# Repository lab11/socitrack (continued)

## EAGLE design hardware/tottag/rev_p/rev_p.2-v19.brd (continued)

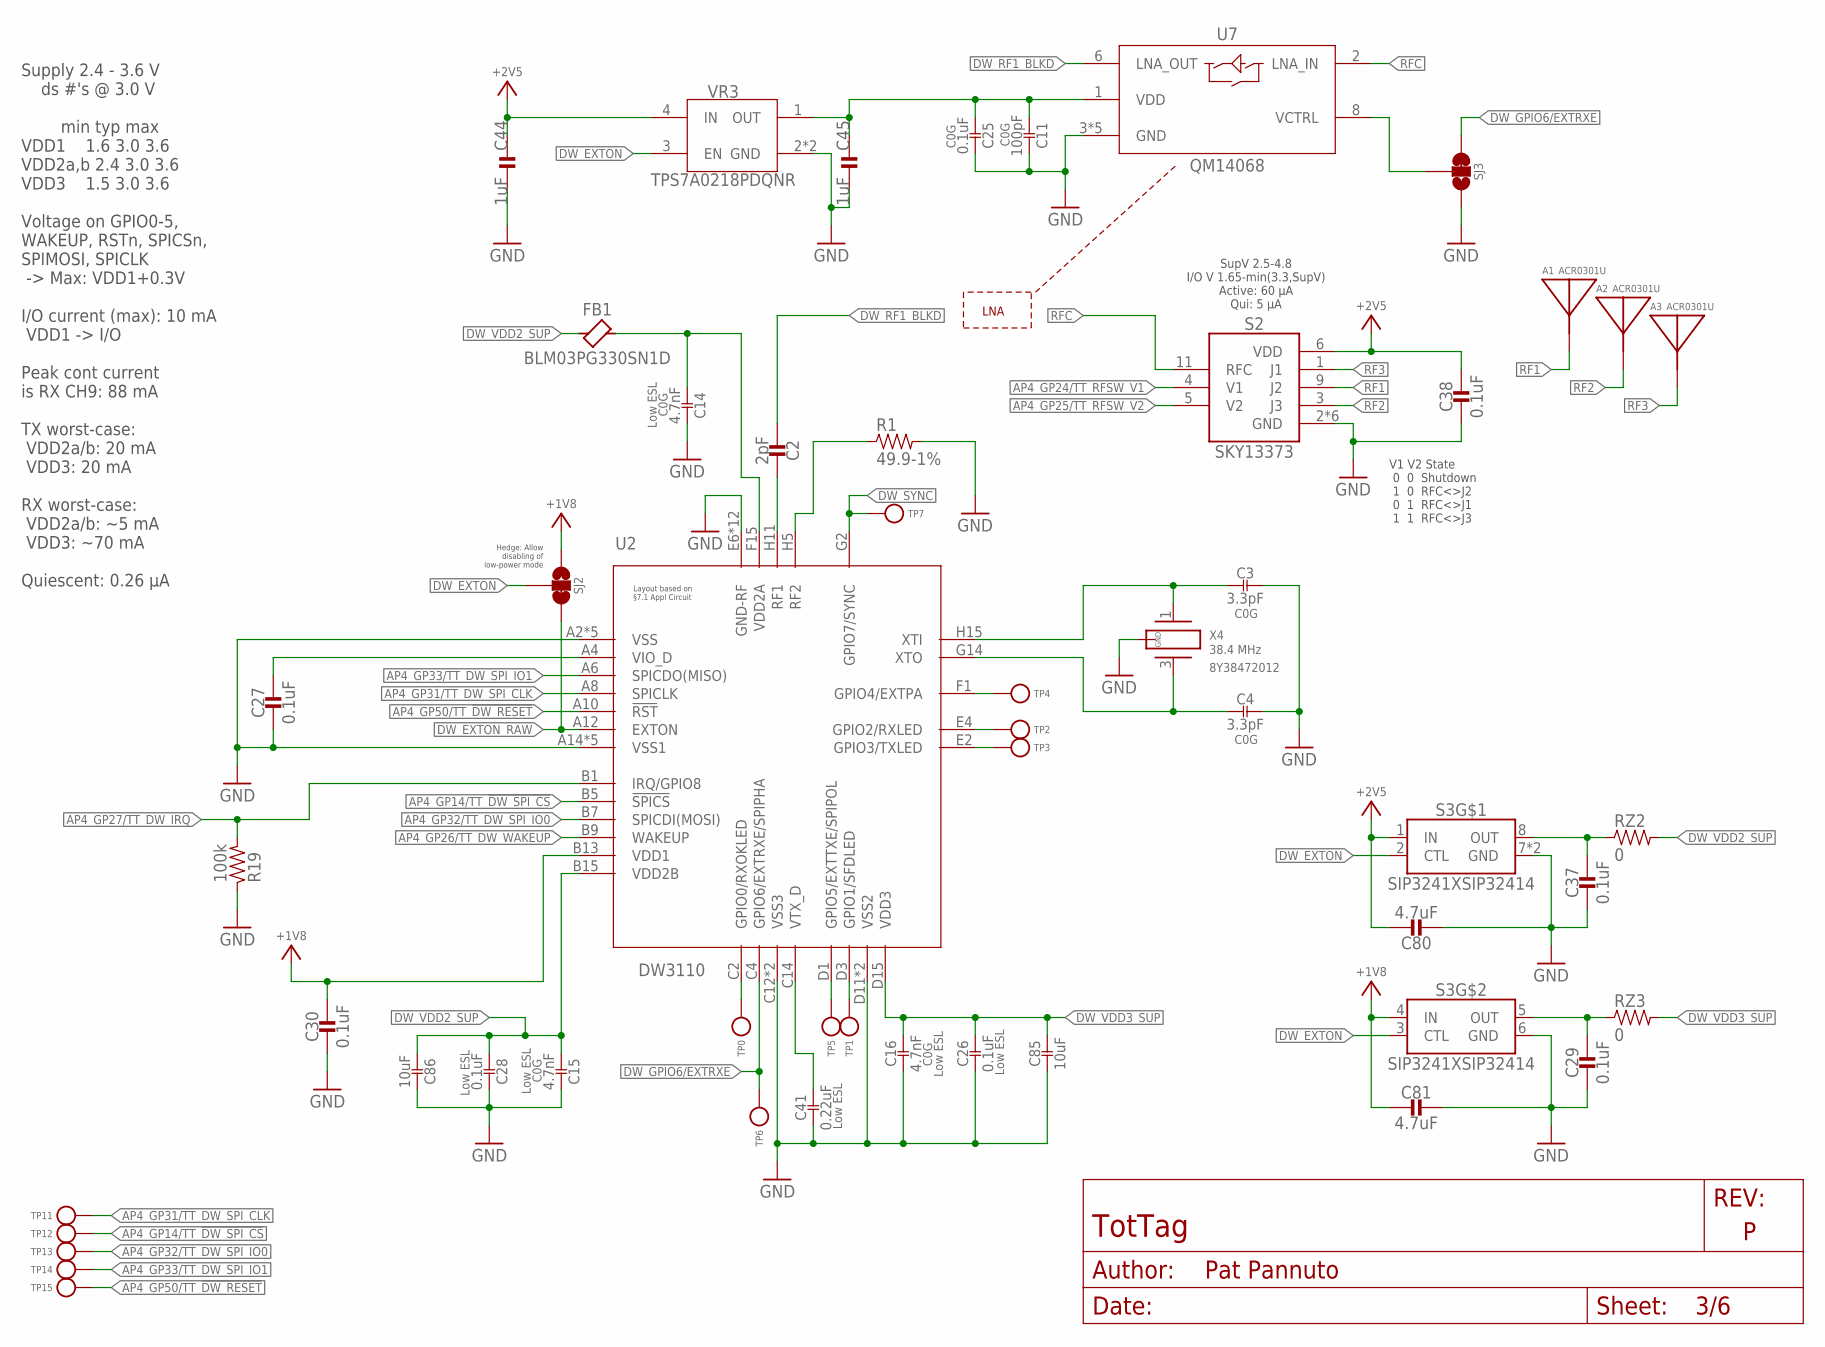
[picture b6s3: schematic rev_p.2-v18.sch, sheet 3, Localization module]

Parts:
A1, A2, A3: ACR0301U
C2: 2pF; 0201_CAP; MPN CBR02C209A5GAC
C3, C4: 3.3pF; SMD_2012M-0805US-C; MPN 600F3R3BT250XT
C11: 100pF; SMD_1005M-0402US-C; MPN C0402C101J3GACTU
C14, C15, C16: 4.7nF; SMD_1608M-0603US-C; MPN C0603C472J5GACTU
C25: 0.1uF; SMD_3216M-1206US-C; MPN GRM31C5C1H104JA01L
C26, C28: 0.1uF; SMD_1608M-0603US-C; MPN C1608X7R1H104K080AA
C27, C29, C30, C37, C38: 0.1uF; 0402_CAP; MPN CL05A104KP5NNNC
C41: 0.22uF; SMD_1608M-0603US-C; MPN C1608X7R1H224K080AB
C44, C45: 1uF; 0201_CAP; MPN GRM033R61A105ME44D
C80, C81: 4.7uF; 0603_CAP; MPN C1608X7S1A475K080AC
C85, C86: 10uF; SMD_1608M-0603US-C; MPN CM105X5R106M25AT
FB1: BLM03PG330SN1D; 0201_FB; MPN BLM03PG330SN1D
R1: 49.9-1%; 0201_RES; MPN ERJ-1GNF49R9C
R19: 100k; 0402_RES; MPN RT0402BRE07100KL
RZ2, RZ3: 0; 0603-RES; MPN RMCF0603ZT0R00
S2: SKY13373
S3: SIP3241XSIP32414; TDFN2X2X0P6-8
SJ2, SJ3: JUMPER-SMT_3_1-NC_TRACE_SILK; SMT-JUMPER_3_1-NC_TRACE_SILK
TP0, TP1, TP2, TP3, TP4, TP5, TP6, TP7, TP11, TP12, TP13, TP14, TP15: TEST-POINT; PAD.03X.03
U2: DW3110; WLCSP52
U7: QM14068
VR3: TPS7A0218PDQNR; 4-XDFN-EP
X4: TXC-8Y; MPN 8Y38472012

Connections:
+1V8: C30.1, C81.2, S3.4 (IN), SJ2.1, U2.B13 (VDD1); also elsewhere on the board
+2V5: C38.1, C44.P$1 (1), C80.1, S2.6 (VDD), S3.1 (IN), VR3.4 (IN); also elsewhere on the board
AP4_GP14/TT_!DW_SPI_CS: TP12.P$1, U2.B5 (!SPICS); also elsewhere on the board
AP4_GP24/TT_RFSW_V1: S2.4 (V1); also elsewhere on the board
AP4_GP25/TT_RFSW_V2: S2.5 (V2); also elsewhere on the board
AP4_GP26/TT_DW_WAKEUP: U2.B9 (WAKEUP); also elsewhere on the board
AP4_GP27/TT_DW_IRQ: R19.2, U2.B1 (IRQ/GPIO8); also elsewhere on the board
AP4_GP31/TT_DW_SPI_CLK: TP11.P$1, U2.A8 (SPICLK); also elsewhere on the board
AP4_GP32/TT_DW_SPI_IO0: TP13.P$1, U2.B7 (SPICDI(MOSI)); also elsewhere on the board
AP4_GP33/TT_DW_SPI_IO1: TP14.P$1, U2.A6 (SPICDO(MISO)); also elsewhere on the board
AP4_GP50/TT_!DW_RESET: TP15.P$1, U2.A10 (!RST); also elsewhere on the board
DW_EXTON: S3.2 (CTL), S3.3 (CTL), SJ2.2, VR3.3 (EN)
DW_EXTON_RAW: SJ2.3, U2.A12 (EXTON)
DW_GPIO4: TP4.P$1, U2.F1 (GPIO4/EXTPA)
DW_GPIO5: TP5.P$1, U2.D1 (GPIO5/EXTTXE/SPIPOL)
DW_GPIO6/EXTRXE: SJ3.3, TP6.P$1, U2.C4 (GPIO6/EXTRXE/SPIPHA)
DW_RF1: C2.P$1 (1), U2.H11 (RF1)
DW_RF1_BLKD: C2.P$2 (2), U7.6 (LNA_OUT)
DW_RF2: R1.1, U2.H5 (RF2)
DW_RXLED: TP2.P$1, U2.E4 (GPIO2/RXLED)
DW_RXOKLED: TP0.P$1, U2.C2 (GPIO0/RXOKLED)
DW_SFDLED: TP1.P$1, U2.D3 (GPIO1/SFDLED)
DW_SYNC: TP7.P$1, U2.G2 (GPIO7/SYNC)
DW_TXLED: TP3.P$1, U2.E2 (GPIO3/TXLED)
DW_VDD2A: C14.P$1, FB1.P$2, U2.F15 (VDD2A)
DW_VDD2_PWROUT: C37.1, RZ2.1, S3.8 (OUT)
DW_VDD2_SUP: C15.P$1, C28.P$1, C86.P$1, FB1.P$1, RZ2.2, U2.B15 (VDD2B)
DW_VDD3_PWROUT: C29.1, RZ3.1, S3.5 (OUT)
DW_VDD3_SUP: C16.P$2, C26.P$2, C85.P$2, RZ3.2, U2.D15 (VDD3)
DW_VIO_D: C27.1, U2.A4 (VIO_D)
DW_VTX_D: C41.P$2, U2.C14 (VTX_D)
DW_XT0: C4.P$1, U2.G14 (XTO), X4.3 (2)
DW_XTI: C3.P$1, U2.H15 (XTI), X4.1
GND: C3.P$2, C4.P$2, C11.P$2, C14.P$2, C15.P$2, C16.P$1, C25.P$2, C26.P$1, C27.2, C28.P$2, C29.2, C30.2, C37.2, C38.2, C41.P$1, C44.P$2 (2), C45.P$2 (2), C80.2, C81.1, C85.P$1, C86.P$2, R1.2, R19.1, S2.2 (GND), S2.7 (GND), S2.8 (GND), S2.10 (GND), S2.12 (GND), S2.PAD (GND), S3.6 (GND), S3.7 (GND), S3.PAD (GND), SJ3.1, U2.A2 (VSS), U2.A14 (VSS1), U2.B3 (VSS), U2.B11 (VSS1), U2.C6 (VSS), U2.C8 (VSS1), U2.C10 (VSS1), U2.C12 (VSS3), U2.D5 (VSS), U2.D7 (VSS), U2.D9 (VSS1), U2.D11 (VSS2), U2.D13 (VSS3), U2.E6 (GND-RF), U2.E10 (GND-RF), U2.E12 (GND-RF), U2.E14 (VSS2), U2.F7 (GND-RF), U2.F9 (GND-RF), U2.G6 (GND-RF), U2.G10 (GND-RF), U2.H1 (GND-RF), U2.H3 (GND-RF), U2.H7 (GND-RF), U2.H9 (GND-RF), U2.H13 (GND-RF), U7.3 (GND), U7.4 (GND), U7.5 (GND), U7.7 (GND), U7.9 (GND), VR3.2 (GND), VR3.PAD (GND), X4.2 (GND), X4.4 (GND); also elsewhere on the board
LNA_VCTRL: SJ3.2, U7.8 (VCTRL)
RF1: A1.FEED, S2.9 (J2)
RF2: A2.FEED, S2.3 (J3)
RF3: A3.FEED, S2.1 (J1)
RFC: S2.11 (RFC), U7.2 (LNA_IN)
VR3_OUT: C11.P$1, C25.P$1, C45.P$1 (1), U7.1 (VDD), VR3.1 (OUT)

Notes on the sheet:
Supply 2.4 - 3.6 V ds #'s @ 3.0 V min typ max VDD1 1.6 3.0 3.6 VDD2a,b 2.4 3.0 3.6 VDD3 1.5 3.0 3.6 Voltage on GPIO0-5, WAKEUP, RSTn, SPICSn, SPIMOSI, SPICLK -> Max: VDD1+0.3V I/O current (max): 10 mA VDD1 -> I/O Peak cont current is RX CH9: 88 mA TX worst-case: VDD2a/b: 20 mA VDD3: 20 mA RX worst-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
SupV 2.5-4.8 I/O V 1.65-min(3.3,SupV) Active: 60 µA Qui: 5 µA
V1 V2 State 0 0 Shutdown 1 0 RFC<>J2 0 1 RFC<>J1 1 1 RFC<>J3
Hedge: Allow disabling of low-power mode
LNA

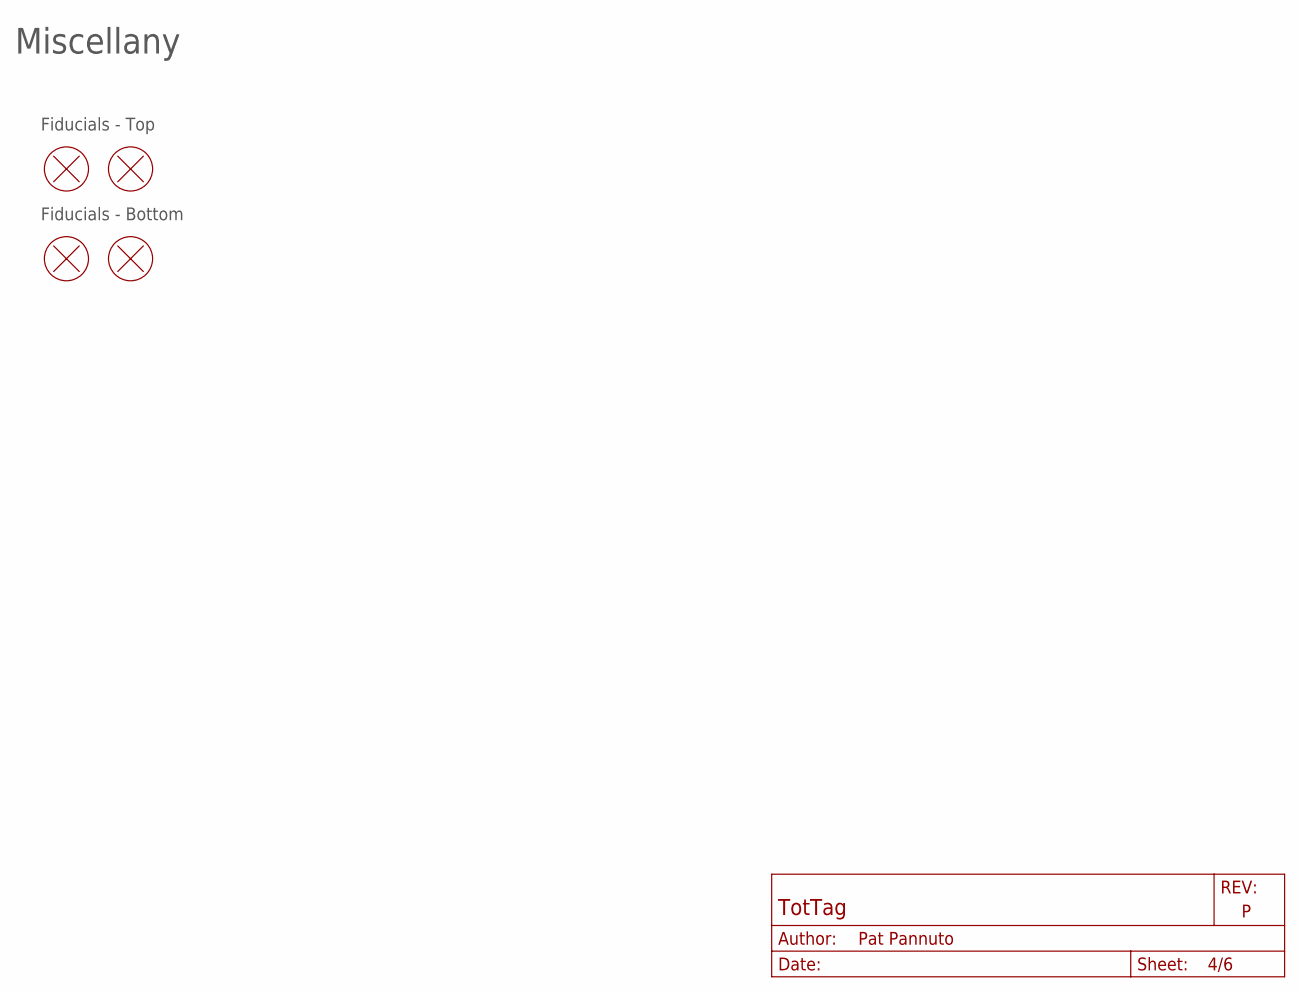
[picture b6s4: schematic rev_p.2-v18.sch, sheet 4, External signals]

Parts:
FD1, FD2, FD3, FD4: FIDUCIAL; FIDUCIAL_1MM-CU_2MM-MASK

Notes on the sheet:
Miscellany
Fiducials - Top
Fiducials - Bottom

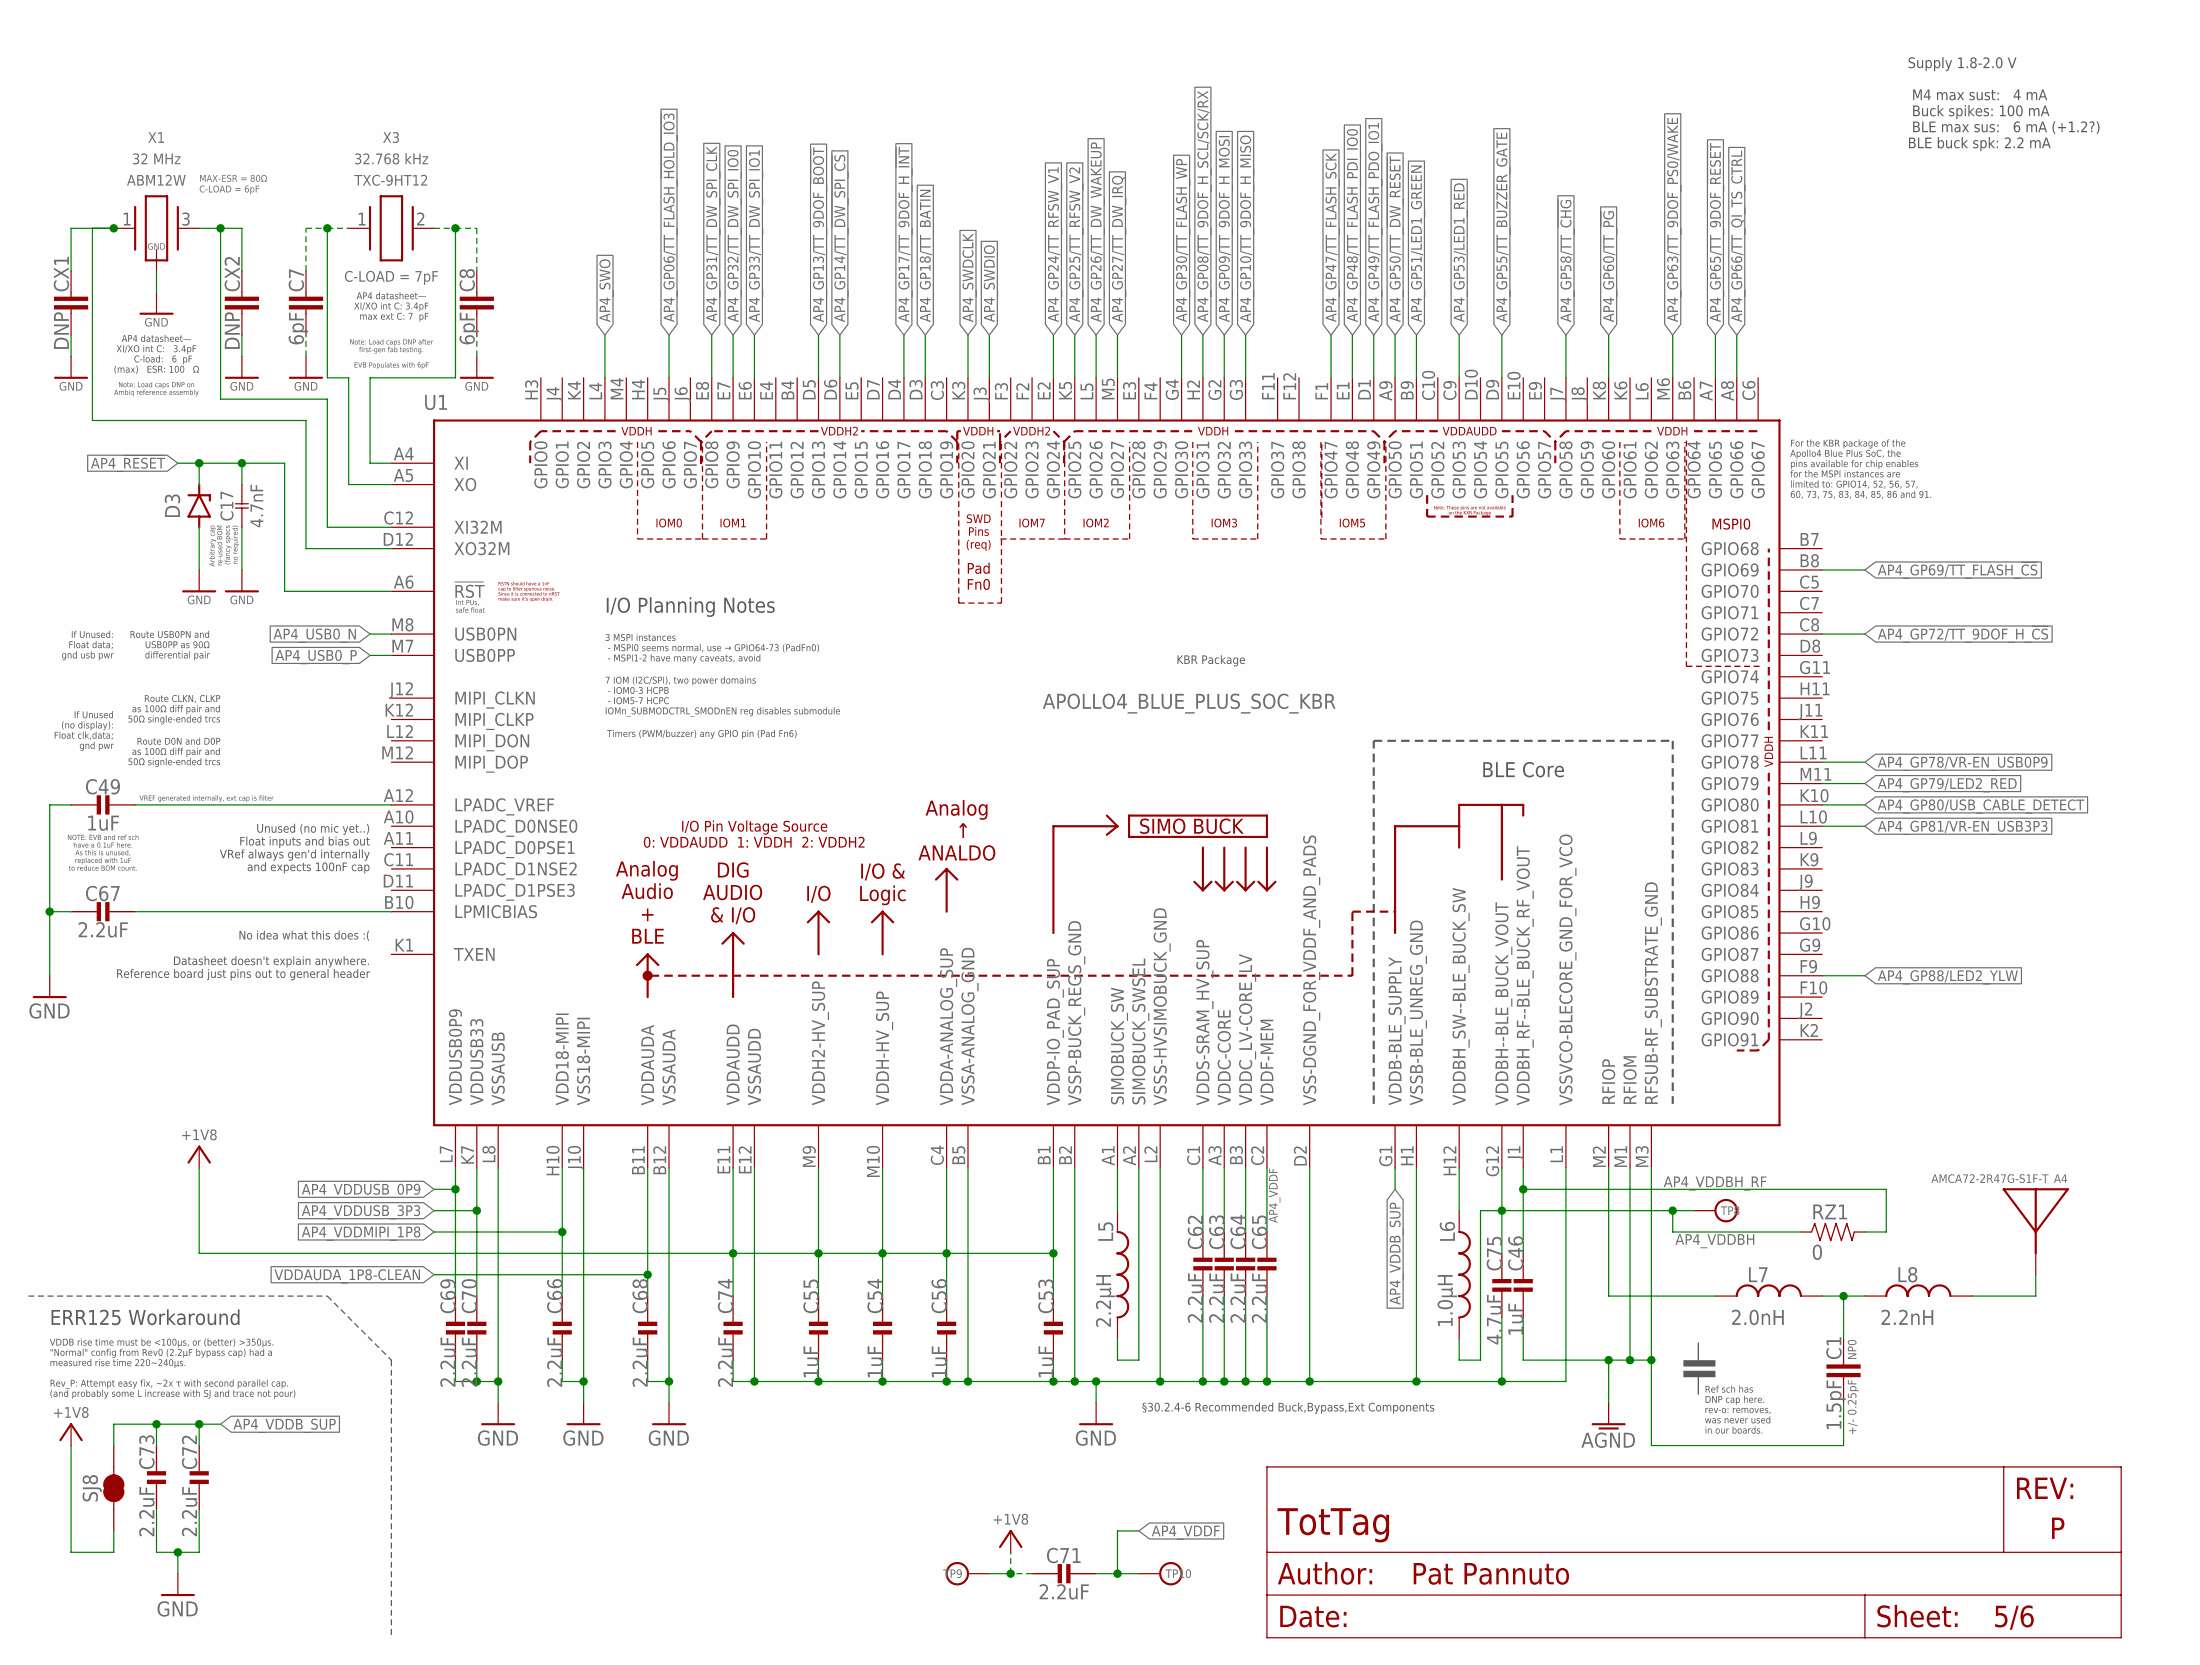
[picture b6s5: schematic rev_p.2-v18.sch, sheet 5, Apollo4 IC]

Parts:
A4: AMCA72-2R47G-S1F-T; AMCA72-2R470G-S1F-T
C1: 1.5pF; CAPC1005X60; TOLERANCE +/- 0.25pF; MPN C0402C159C5GACTU
C7, C8: 6pF; CAPC1005X60; MPN GCM1555C1H6R0BA16D
C17: 4.7nF; SMD_1608M-0603US-C; MPN C0603C472J5GACTU
C46, C49, C53, C54, C55, C56: 1uF; 0201_CAP; MPN GRM033R61A105ME44D
C62, C63, C64, C65, C66, C67, C68, C69, C70, C71, C72, C73, C74: 2.2uF; 0201_CAP; MPN GRM033R61A225KE47D
C75: 4.7uF; 0402_CAP; MPN CL05A475MP5NRNC
CX1, CX2: DNP; CAPC1005X60
D3: ZENER; SODFL1608X70; MPN PESD5V0X1UB,135
L5: 2.2µH; 0805_CAP; MPN DFE201210U-2R2M=P2
L6: 1.0µH; 0603_CAP; MPN MCKK1608T1R0MN
L7: 2.0nH; INDC1006X60N; TOLERANCE +/- 0.1 nH; MPN LQG15HS2N0B02D
L8: 2.2nH; INDC1006X60N; TOLERANCE +/- 0.1 nH; MPN LQG15HN2N2B02D
RZ1: 0; 0402_RES; MPN RMCF0402ZT0R00
SJ8: JUMPER-SMT_2_NC_TRACE_SILK; SMT-JUMPER_2_NC_TRACE_SILK
TP8, TP9, TP10: TEST-POINT; PAD.03X.03
U1: APOLLO4_BLUE_PLUS_SOC_KBR; APOLLO4_BLUE_SOC_BGA
X1: ABM12W; MPN ABM12W-32.0000MHZ-6-D1X-T3
X3: TXC-9HT12; MPN 9HT12-32.768KDZY-T

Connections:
+1V8: C53.P$1 (1), C54.P$1 (1), C55.P$1 (1), C56.P$1 (1), C71.P$2 (2), C74.P$1 (1), SJ8.1, TP9.P$1, U1.B1 (VDDP-IO_PAD_SUP), U1.C4 (VDDA-ANALOG_SUP), U1.E11 (VDDAUDD), U1.M9 (VDDH2-HV_SUP), U1.M10 (VDDH-HV_SUP); also elsewhere on the board
AGND: C1.2, C46.P$2 (2), U1.M1 (RFIOM), U1.M3 (RFSUB-RF_SUBSTRATE_GND)
AP4_!RESET: C17.P$2, D3.1 (C), U1.A6 (!RST); also elsewhere on the board
AP4_GP06/TT_FLASH_!HOLD_IO3: U1.J5 (GPIO6); also elsewhere on the board
AP4_GP08/TT_9DOF_H_SCL/SCK/RX: U1.H2 (GPIO31); also elsewhere on the board
AP4_GP09/TT_9DOF_H_MOSI: U1.G2 (GPIO32); also elsewhere on the board
AP4_GP10/TT_9DOF_H_MISO: U1.G3 (GPIO33); also elsewhere on the board
AP4_GP13/TT_9DOF_!BOOT: U1.D5 (GPIO13); also elsewhere on the board
AP4_GP14/TT_!DW_SPI_CS: U1.D6 (GPIO14); also elsewhere on the board
AP4_GP17/TT_9DOF_H_!INT: U1.D4 (GPIO17); also elsewhere on the board
AP4_GP18/TT_BATIN: U1.D3 (GPIO18); also elsewhere on the board
AP4_GP24/TT_RFSW_V1: U1.E2 (GPIO24); also elsewhere on the board
AP4_GP25/TT_RFSW_V2: U1.K5 (GPIO25); also elsewhere on the board
AP4_GP26/TT_DW_WAKEUP: U1.L5 (GPIO26); also elsewhere on the board
AP4_GP27/TT_DW_IRQ: U1.M5 (GPIO27); also elsewhere on the board
AP4_GP30/TT_FLASH_!WP: U1.G4 (GPIO30); also elsewhere on the board
AP4_GP31/TT_DW_SPI_CLK: U1.E8 (GPIO8); also elsewhere on the board
AP4_GP32/TT_DW_SPI_IO0: U1.E7 (GPIO9); also elsewhere on the board
AP4_GP33/TT_DW_SPI_IO1: U1.E6 (GPIO10); also elsewhere on the board
AP4_GP47/TT_FLASH_SCK: U1.F1 (GPIO47); also elsewhere on the board
AP4_GP48/TT_FLASH_PDI_IO0: U1.E1 (GPIO48); also elsewhere on the board
AP4_GP49/TT_FLASH_PDO_IO1: U1.D1 (GPIO49); also elsewhere on the board
AP4_GP50/TT_!DW_RESET: U1.A9 (GPIO50); also elsewhere on the board
AP4_GP51/LED1_GREEN: U1.B9 (GPIO51); also elsewhere on the board
AP4_GP53/LED1_RED: U1.C9 (GPIO53); also elsewhere on the board
AP4_GP55/TT_BUZZER_GATE: U1.D9 (GPIO55); also elsewhere on the board
AP4_GP58/TT_!CHG: U1.J7 (GPIO58); also elsewhere on the board
AP4_GP60/TT_!PG: U1.K8 (GPIO60); also elsewhere on the board
AP4_GP63/TT_9DOF_PS0/WAKE: U1.M6 (GPIO63); also elsewhere on the board
AP4_GP65/TT_9DOF_!RESET: U1.A7 (GPIO65); also elsewhere on the board
AP4_GP66/TT_QI_TS_CTRL: U1.A8 (GPIO66); also elsewhere on the board
AP4_GP69/TT_FLASH_!CS: U1.B8 (GPIO69); also elsewhere on the board
AP4_GP72/TT_9DOF_H_!CS: U1.C8 (GPIO72); also elsewhere on the board
AP4_GP78/VR-EN_USB0P9: U1.L11 (GPIO78); also elsewhere on the board
AP4_GP79/LED2_RED: U1.M11 (GPIO79); also elsewhere on the board
AP4_GP80/USB_CABLE_DETECT: U1.K10 (GPIO80); also elsewhere on the board
AP4_GP81/VR-EN_USB3P3: U1.L10 (GPIO81); also elsewhere on the board
AP4_GP88/LED2_YLW: U1.F9 (GPIO88); also elsewhere on the board
AP4_LPADC_VREF: C49.P$2 (2), U1.A12 (LPADC_VREF)
AP4_LPMICBIAS: C67.P$2 (2), U1.B10 (LPMICBIAS)
AP4_RFIOP1: L7.1, U1.M2 (RFIOP)
AP4_SWDCLK: U1.K3 (GPIO20); also elsewhere on the board
AP4_SWDIO: U1.J3 (GPIO21); also elsewhere on the board
AP4_SWO: U1.L4 (GPIO3); also elsewhere on the board
AP4_USB0_N: U1.M8 (USB0PN); also elsewhere on the board
AP4_USB0_P: U1.M7 (USB0PP); also elsewhere on the board
AP4_VDDBH: C75.1, L6.2, RZ1.1, TP8.P$1, U1.G12 (VDDBH--BLE_BUCK_VOUT)
AP4_VDDBH_RF: C46.P$1 (1), RZ1.2, U1.J1 (VDDBH_RF--BLE_BUCK_RF_VOUT)
AP4_VDDBH_SW: L6.1, U1.H12 (VDDBH_SW--BLE_BUCK_SW)
AP4_VDDB_SUP: C72.P$1 (1), C73.P$1 (1), SJ8.2, U1.G1 (VDDB-BLE_SUPPLY)
AP4_VDDC: C63.P$1 (1), U1.A3 (VDDC-CORE)
AP4_VDDC_LV: C64.P$1 (1), U1.B3 (VDDC_LV-CORE_LV)
AP4_VDDF: C65.P$1 (1), C71.P$1 (1), TP10.P$1, U1.C2 (VDDF-MEM)
AP4_VDDMIPI_1P8: C66.P$1 (1), U1.H10 (VDD18-MIPI); also elsewhere on the board
AP4_VDDS: C62.P$1 (1), U1.C1 (VDDS-SRAM_HV_SUP)
AP4_VDDUSB_0P9: C69.P$1 (1), U1.L7 (VDDUSB0P9); also elsewhere on the board
AP4_VDDUSB_3P3: C70.P$1 (1), U1.K7 (VDDUSB33); also elsewhere on the board
AP4_XI: C8.1, U1.A4 (XI), X3.2
AP4_XI32M: CX2.1, U1.C12 (XI32M), X1.3 (2)
AP4_XO: C7.1, U1.A5 (XO), X3.1
AP4_XO32M: CX1.1, U1.D12 (XO32M), X1.1
BLE_RFOUT: A4.S1, L8.2
GND: C7.2, C8.2, C17.P$1, C49.P$1 (1), C53.P$2 (2), C54.P$2 (2), C55.P$2 (2), C56.P$2 (2), C62.P$2 (2), C63.P$2 (2), C64.P$2 (2), C65.P$2 (2), C66.P$2 (2), C67.P$1 (1), C68.P$2 (2), C69.P$2 (2), C70.P$2 (2), C72.P$2 (2), C73.P$2 (2), C74.P$2 (2), C75.2, CX1.2, CX2.2, D3.2 (A), U1.B2 (VSSP-BUCK_REGS_GND), U1.B5 (VSSA-ANALOG_GND), U1.B12 (VSSAUDA), U1.D2 (VSS-DGND_FOR_VDDF_AND_PADS), U1.E12 (VSSAUDD), U1.H1 (VSSB-BLE_UNREG_GND), U1.J10 (VSS18-MIPI), U1.L1 (VSSVCO-BLECORE_GND_FOR_VCO), U1.L2 (VSSS-HVSIMOBUCK_GND), U1.L8 (VSSAUSB), X1.2 (GND), X1.4 (GND); also elsewhere on the board
unnamed: C1.1, L7.2, L8.1
SIMOBUCK_SW: L5.P$1 (1), U1.A1 (SIMOBUCK_SW)
SIMOBUCK_SWSEL: L5.P$2 (2), U1.A2 (SIMOBUCK_SWSEL)
VDDAUDA_1P8-CLEAN: C68.P$1 (1), U1.B11 (VDDAUDA); also elsewhere on the board

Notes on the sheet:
Supply 1.8-2.0 V M4 max sust: 4 mA Buck spikes: 100 mA BLE max sus: 6 mA (+1.2?) BLE buck spk: 2.2 mA
Note: Load caps DNP on Ambiq reference assembly
Int PUs, safe float
If Unused: Float data; gnd usb pwr
If Unused (no display): Float clk,data; gnd pwr
Unused (no mic yet..) Float inputs and bias out VRef always gen'd internally and expects 100nF cap
No idea what this does :( Datasheet doesn't explain anywhere. Reference board just pins out to general header
I/O Planning Notes
3 MSPI instances - MSPI0 seems normal, use → GPIO64-73 (PadFn0) - MSPI1-2 have many caveats, avoid
7 IOM (I2C/SPI), two power domains - IOM0-3 HCPB - IOM5-7 HCPC IOMn_SUBMODCTRL_SMODnEN reg disables submodule
MSPI0
IOM0
IOM1
Timers (PWM/buzzer) any GPIO pin (Pad Fn6)
KBR Package
For the KBR package of the Apollo4 Blue Plus SoC, the pins available for chip enables for the MSPI instances are limited to: GPIO14, 52, 56, 57, 60, 73, 75, 83, 84, 85, 86 and 91.
§30.2.4-6 Recommended Buck,Bypass,Ext Components
SWD Pins (req)
VREF generated internally, ext cap is filter
IOM3
AP4 datasheet— XI/XO int C: 3.4pF max ext C: 7 pF
AP4 datasheet— XI/XO int C: 3.4pF C-load: 6 pF (max) ESR: 100 Ω
Pad Fn0
Note: Load caps DNP after first-gen fab testing. EVB Populates with 6pF
Route USB0PN and USB0PP as 90Ω differential pair
Route CLKN, CLKP as 100Ω diff pair and 50Ω single-ended trcs
Route D0N and D0P as 100Ω diff pair and 50Ω signle-ended trcs
NOTE: EVB and ref sch have a 0.1uF here. As this is unused, replaced with 1uF to reduce BOM count.
IOM2
IOM5
IOM6
IOM7
Ref sch has DNP cap here. rev-o: removes, was never used in our boards.
VDDB rise time must be <100µs, or (better) >350µs. "Normal" config from Rev0 (2.2µF bypass cap) had a measured rise time 220~240µs. Rev_P: Attempt easy fix, ~2x τ with second parallel cap. (and probably some L increase with SJ and trace not pour)
ERR125 Workaround
Arbitrary cap re-used BOM (fancy specs no required)

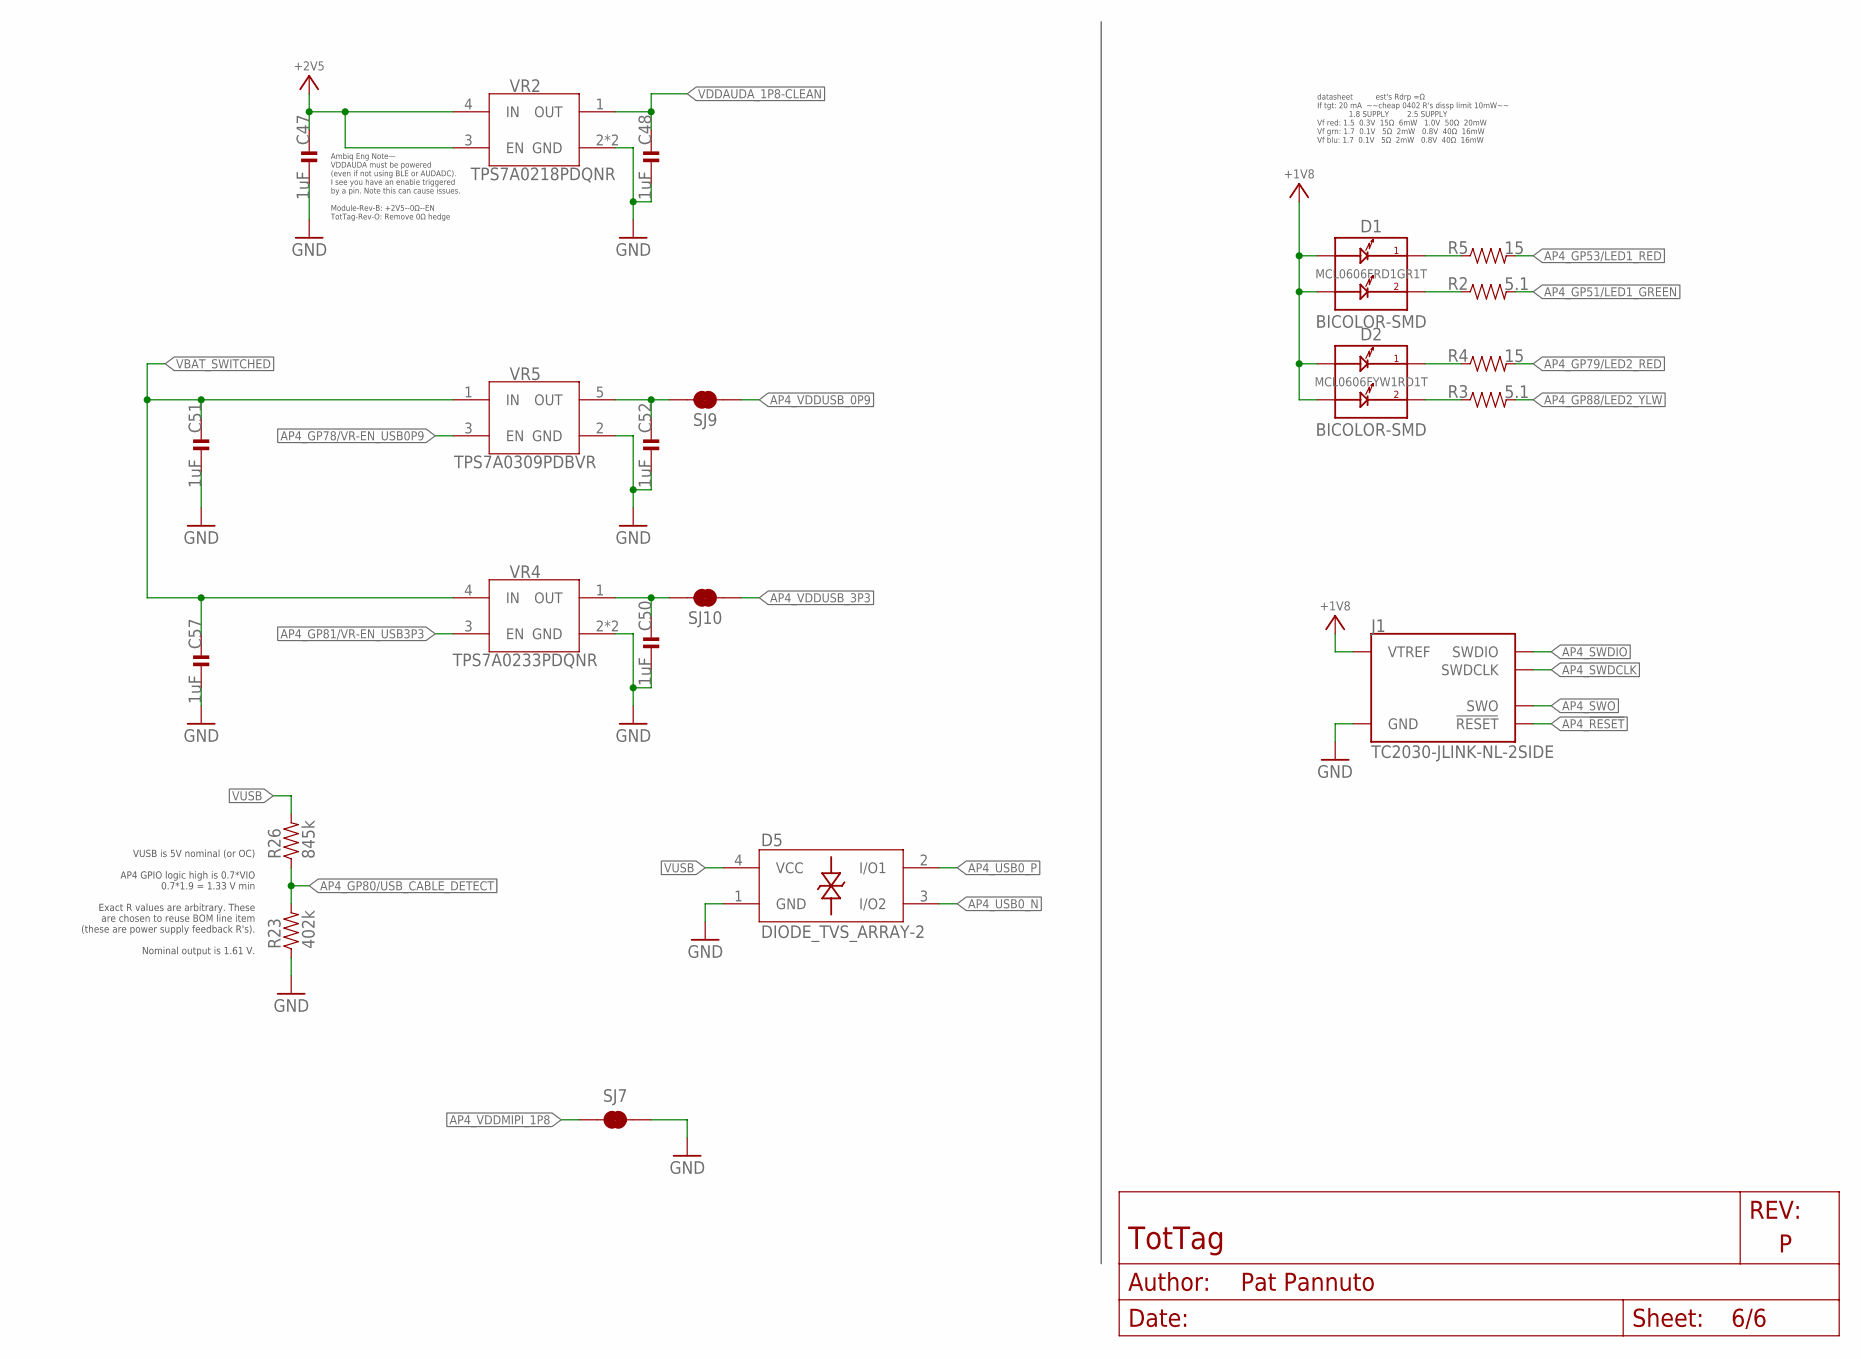
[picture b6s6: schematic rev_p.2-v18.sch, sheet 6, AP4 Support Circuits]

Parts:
C47, C48, C50, C51, C52, C57: 1uF; 0201_CAP; MPN GRM033R61A105ME44D
D1: BICOLOR-SMD; LED-0606; MPN MCL0606FRD1GR1T
D2: BICOLOR-SMD; LED-0606; MPN MCL0606FYW1RD1T
D5: DIODE_TVS_ARRAY-2; SOT143B
J1: TC2030-JLINK-NL-2SIDE; TC2030-IDC-NL-2SIDE
R2, R3: 5.1; 0402_RES; MPN RC0402JR-075R1L
R4, R5: 15; 0402_RES; MPN RC0402JR-0715RL
R23: 402k; 0201_RES; MPN ERJ-1GNF4023C
R26: 845k; 0201_RES; MPN ERJ-1GNF8453C
SJ7, SJ9, SJ10: JUMPER-SMT_2_NC_TRACE_SILK; SMT-JUMPER_2_NC_TRACE_SILK
VR2: TPS7A0218PDQNR; 4-XDFN-EP
VR4: TPS7A0233PDQNR; 4-XDFN-EP
VR5: TPS7A0309PDBVR; DBV0005A--SOT23-5-VARIANT

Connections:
+1V8: D1.A1, D1.A2, D2.A1, D2.A2, J1.1 (VTREF), J1.B1 (VTREF); also elsewhere on the board
+2V5: C47.P$1 (1), VR2.3 (EN), VR2.4 (IN); also elsewhere on the board
AP4_!RESET: J1.3 (!RESET), J1.B3 (!RESET); also elsewhere on the board
AP4_GP51/LED1_GREEN: R2.2; also elsewhere on the board
AP4_GP53/LED1_RED: R5.2; also elsewhere on the board
AP4_GP78/VR-EN_USB0P9: VR5.3 (EN); also elsewhere on the board
AP4_GP79/LED2_RED: R4.2; also elsewhere on the board
AP4_GP80/USB_CABLE_DETECT: R23.2, R26.1; also elsewhere on the board
AP4_GP81/VR-EN_USB3P3: VR4.3 (EN); also elsewhere on the board
AP4_GP88/LED2_YLW: R3.2; also elsewhere on the board
AP4_LED2_BLUE_COMM: D1.C1, R5.1
AP4_LED_BLUE_COMM: D2.C2, R3.1
AP4_LED_GREEN_COMM: D2.C1, R4.1
AP4_LED_RED_COMM: D1.C2, R2.1
AP4_SWDCLK: J1.4 (SWDCLK), J1.B4 (SWDCLK); also elsewhere on the board
AP4_SWDIO: J1.2 (SWDIO), J1.B2 (SWDIO); also elsewhere on the board
AP4_SWO: J1.6 (SWO), J1.B6 (SWO); also elsewhere on the board
AP4_USB0_N: D5.3 (I/O2); also elsewhere on the board
AP4_USB0_P: D5.2 (I/O1); also elsewhere on the board
AP4_VDDMIPI_1P8: SJ7.1; also elsewhere on the board
AP4_VDDUSB_0P9: SJ9.1; also elsewhere on the board
AP4_VDDUSB_3P3: SJ10.1; also elsewhere on the board
GND: C47.P$2 (2), C48.P$2 (2), C50.P$2 (2), C51.P$2 (2), C52.P$2 (2), C57.P$2 (2), D5.1 (GND), J1.5 (GND), J1.B5 (GND), R23.1, SJ7.2, VR2.2 (GND), VR2.PAD (GND), VR4.2 (GND), VR4.PAD (GND), VR5.2 (GND); also elsewhere on the board
VBAT_SWITCHED: C51.P$1 (1), C57.P$1 (1), VR4.4 (IN), VR5.1 (IN); also elsewhere on the board
VDDAUDA_1P8-CLEAN: C48.P$1 (1), VR2.1 (OUT); also elsewhere on the board
VDDUSB_0P9: C52.P$1 (1), SJ9.2, VR5.5 (OUT)
VDDUSB_3P3: C50.P$1 (1), SJ10.2, VR4.1 (OUT)
VUSB: D5.4 (VCC), R26.2; also elsewhere on the board

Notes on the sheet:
Ambiq Eng Note— VDDAUDA must be powered (even if not using BLE or AUDADC). I see you have an enable triggered by a pin. Note this can cause issues. Module-Rev-B: +2V5--0Ω--EN TotTag-Rev-O: Remove 0Ω hedge
datasheet est's Rdrp =Ω If tgt: 20 mA ~~cheap 0402 R's dissp limit 10mW~~ 1.8 SUPPLY 2.5 SUPPLY Vf red: 1.5 0.3V 15Ω 6mW 1.0V 50Ω 20mW Vf grn: 1.7 0.1V 5Ω 2mW 0.8V 40Ω 16mW Vf blu: 1.7 0.1V 5Ω 2mW 0.8V 40Ω 16mW
VUSB is 5V nominal (or OC) AP4 GPIO logic high is 0.7*VIO 0.7*1.9 = 1.33 V min Exact R values are arbitrary. These are chosen to reuse BOM line item (these are power supply feedback R's). Nominal output is 1.61 V.

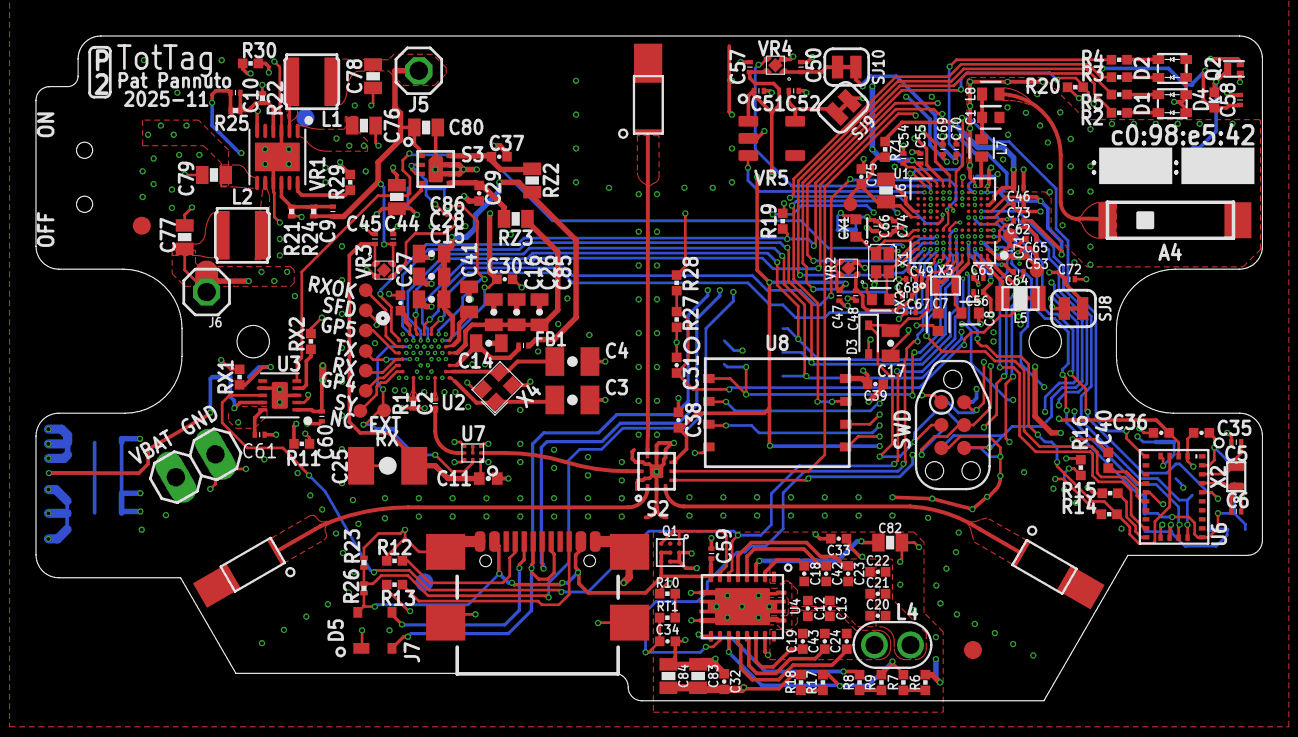
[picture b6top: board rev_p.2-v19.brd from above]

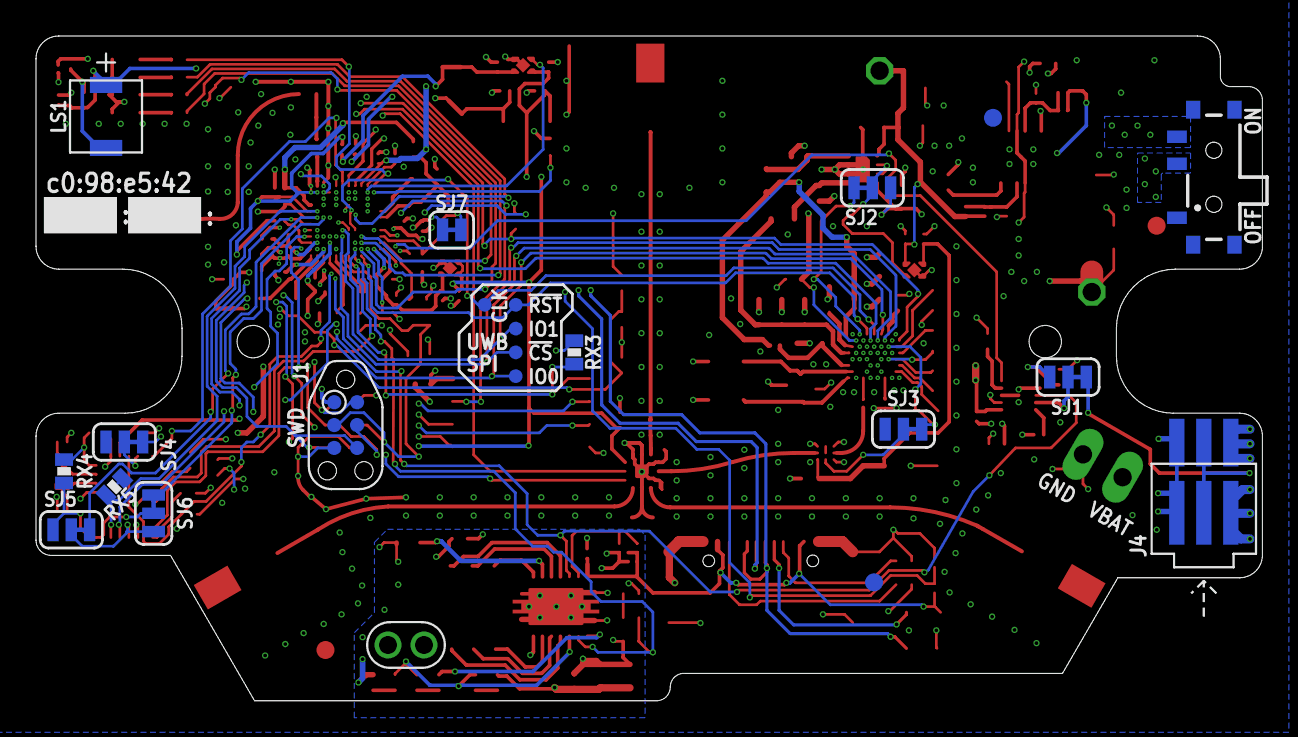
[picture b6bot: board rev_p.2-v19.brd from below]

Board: 4 copper layers, 68.1 x 36.9 mm, 202 parts (20 on the bottom side), 145 nets.

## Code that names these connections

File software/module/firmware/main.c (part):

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	// We explicitly also allow this to happen when LEDs are disabled to signal an error

    // Turn all LEDs off
    GPIO_SetBits(STM_LED_RED_PORT, STM_LED_RED_PIN | STM_LED_BLUE_PIN | STM_LED_GREEN_PIN);

	// Start blinking RED
	while (1) {
		GPIO_WriteBit(STM_LED_RED_PORT, STM_LED_RED_PIN, Bit_SET);
		mDelay(250);
		GPIO_WriteBit(STM_LED_RED_PORT, STM_LED_RED_PIN, Bit_RESET);
		mDelay(250);
	}
#endif
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	GPIO_InitTypeDef GPIO_InitStructure_B;
	RCC_AHBPeriphClockCmd(STM_GPIO3_CLK, ENABLE);
#if (BOARD_V == SQUAREPOINT)
	GPIO_InitStructure_B.GPIO_Pin 	= STM_GPIO3_PIN | STM_LED_RED_PIN | STM_LED_BLUE_PIN | STM_LED_GREEN_PIN;
#elif (BOARD_V == TRIPOINT)
    GPIO_InitStructure_B.GPIO_Pin 	= STM_GPIO3_PIN;
#endif
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#if (BOARD_V == SQUAREPOINT)
#ifndef STM_DISABLE_LEDS
    // Signal init by turning on WHITE
	GPIO_WriteBit(STM_LED_RED_PORT,   STM_LED_RED_PIN,   Bit_RESET);
    GPIO_WriteBit(STM_LED_BLUE_PORT,  STM_LED_BLUE_PIN,  Bit_RESET);
    GPIO_WriteBit(STM_LED_GREEN_PORT, STM_LED_GREEN_PIN, Bit_RESET);
#else
    // Turn all of them (permanently) off
    GPIO_WriteBit(STM_LED_RED_PORT,   STM_LED_RED_PIN,   Bit_SET);
    GPIO_WriteBit(STM_LED_BLUE_PORT,  STM_LED_BLUE_PIN,  Bit_SET);
    GPIO_WriteBit(STM_LED_GREEN_PORT, STM_LED_GREEN_PIN, Bit_SET);
#endif
#endif

	//Initialize UART1 on GPIO0 and GPIO1
    // Tx: GPIO1 -> Pin 27 -> PB6
    // Rx: GPIO4 -> Pin 28 -> PB7
    /*USART_InitTypeDef usartConfig;
    GPIO_InitTypeDef gpioConfig;

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#if (BOARD_V == SQUAREPOINT)
#ifndef STM_DISABLE_LEDS
	// Signal that internal setup is finished by setting RED
	GPIO_WriteBit(STM_LED_BLUE_PORT,  STM_LED_BLUE_PIN,  Bit_SET);
    GPIO_WriteBit(STM_LED_GREEN_PORT, STM_LED_GREEN_PIN, Bit_SET);
#endif
#endif

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#if (BOARD_V == SQUAREPOINT)
#ifndef STM_DISABLE_LEDS
	// Signal normal operation by turning on BLUE
	GPIO_WriteBit(STM_LED_RED_PORT,  STM_LED_RED_PIN,  Bit_SET);
	GPIO_WriteBit(STM_LED_BLUE_PORT, STM_LED_BLUE_PIN, Bit_RESET);
#endif
#endif

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
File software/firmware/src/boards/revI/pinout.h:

#ifndef __PINOUT_HEADER_H__
#define __PINOUT_HEADER_H__

// Hardware Revision ID
#include "revisions.h"
#define REVISION_ID                                 REVISION_I

// Battery
#define PIN_BATTERY_VOLTAGE                         18
#define PIN_BATTERY_VOLTAGE_FUNCTION                AM_HAL_PIN_18_ADCSE1
#define PIN_BATTERY_VOLTAGE_ADC_CHANNEL             AM_HAL_ADC_SLOT_CHSEL_SE1
#define PIN_BATTERY_CHARGING_STATUS                 58
#define PIN_BATTERY_INPUT_POWER_GOOD                60
#define PIN_BATTERY_CHARGE_COMPLETE_SIGNAL          47
#define VOLTAGE_DIVIDER_LOWER                       33
#define VOLTAGE_DIVIDER_UPPER                       51

// Buzzer
#define PIN_BUZZER_DRIVER                           54

// DecaWave Radio
#define RADIO_SPI_NUMBER                            0
#define PIN_RADIO_SPI_SCK                           5
#define PIN_RADIO_SPI_MISO                          7
#define PIN_RADIO_SPI_MOSI                          6
#define PIN_RADIO_SPI_CS                            29
#define PIN_RADIO_INTERRUPT                         27
#define PIN_RADIO_RESET                             49
#define PIN_RADIO_WAKEUP                            26
#define PIN_RADIO_ANTENNA_SELECT1                   24
#define PIN_RADIO_ANTENNA_SELECT2                   25
#define PIN_RADIO_SPI_SCK_FUNCTION                  AM_HAL_PIN_5_M0SCK
#define PIN_RADIO_SPI_MISO_FUNCTION                 AM_HAL_PIN_7_M0MISO
#define PIN_RADIO_SPI_MOSI_FUNCTION                 AM_HAL_PIN_6_M0MOSI
#define PIN_RADIO_SPI_CS_FUNCTION                   AM_HAL_PIN_29_NCE29

// IMU
#define IMU_I2C_NUMBER                              1
#define IMU_I2C_ADDRESS                             0x29
#define PIN_IMU_I2C_SCL                             8
#define PIN_IMU_I2C_SDA                             9
#define PIN_IMU_I2C_SCL_FUNCTION                    AM_HAL_PIN_8_M1SCL
#define PIN_IMU_I2C_SDA_FUNCTION                    AM_HAL_PIN_9_M1SDAWIR3
#define PIN_IMU_INTERRUPT                           17
#define PIN_IMU_RESET                               48

// LEDs
#define PIN_LED1_RED                                52
#define PIN_LED1_GREEN                              80
#define PIN_LED2_RED                                76
#define PIN_LED2_YELLOW                             81

// Logging
#define PIN_SWO                                     67
#define PIN_SWO_FUNCTION                            AM_HAL_PIN_67_SWO

// Memory Storage (SPI)
#define STORAGE_SPI_NUMBER                          3
#define PIN_STORAGE_SPI_SCK                         31
#define PIN_STORAGE_SPI_MISO                        33
#define PIN_STORAGE_SPI_MOSI                        32
#define PIN_STORAGE_SPI_CS                          63
#define PIN_STORAGE_SPI_SCK_FUNCTION                AM_HAL_PIN_31_M3SCK
#define PIN_STORAGE_SPI_MISO_FUNCTION               AM_HAL_PIN_33_M3MISO
#define PIN_STORAGE_SPI_MOSI_FUNCTION               AM_HAL_PIN_32_M3MOSI
#define PIN_STORAGE_SPI_CS_FUNCTION                 AM_HAL_PIN_63_NCE63
#define PIN_STORAGE_WRITE_PROTECT                   66
#define PIN_STORAGE_HOLD                            67
#define MEMORY_PAGE_SIZE_BYTES                      2048
#define MEMORY_BLOCK_COUNT                          1024
#define MEMORY_ECC_BYTES_PER_PAGE                   64
#define STORAGE_DEVICE_ID                           { 0xEF, 0xBA, 0x21 }

// Timers
#define BUZZER_TIMER_NUMBER                         0
#define RADIO_WAKEUP_TIMER_NUMBER                   2
#define RADIO_WAKEUP_TIMER_TICK_RATE_HZ             (AM_HAL_CLKGEN_FREQ_MAX_HZ / 16)
#define BLE_SCANNING_TIMER_NUMBER                   3
#define BLE_SCANNING_TIMER_TICK_RATE_HZ             (AM_HAL_CLKGEN_FREQ_MAX_HZ / 16)

#endif  // #ifndef __PINOUT_HEADER_H__
